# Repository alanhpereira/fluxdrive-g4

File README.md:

# fluxdrive-g4

Firmware, PC software and hardware design of a field-oriented-control (FOC) driver for 3-phase BLDC/PMSM motors, built as a graduation thesis (TCC) project.

- **Controller:** STSPIN32G4 (STM32G431 Cortex-M4F at 170 MHz with an integrated 3-phase gate driver), six 100 V MOSFETs, three 2 mΩ low-side shunts.
- **Control:** current loop at 25 kHz; speed and position loops at 2.5 kHz. Commutation from an MT6835 21-bit magnetic encoder, from the encoder with a back-EMF flux observer blended in at speed, or sensorless (high-frequency injection at standstill, the observer at speed).
- **Links:** USB-C (virtual COM port: telemetry, configuration, calibration) and CANopen (CiA 301 node, CiA 402 drive profile: PP, PV, HM, CSP, CSV, CST).
- **Protections:** overcurrent, over/undervoltage, regen clamp, overspeed, encoder loss, gate-driver faults. Stops coast instead of short-braking a spinning motor.
- **PC software:** a Python/Qt GUI with live plots, a parameter editor, a calibration wizard and a CANopen master, plus a CANopen test runner.

## Ratings and status

| | Designed for | Tested up to |
|---|---|---|
| Bus voltage | 70 V | 32 V |
| Phase current (continuous) | 15 A | 10 A |

This is a working prototype from a graduation thesis, not a finished product. Everything above the tested values is untested: the bridge MOSFETs are rated 100 V, but thermal performance, layout and protection behaviour at 70 V / 15 A have not been verified. The firmware defaults are conservative: overcurrent trip `imax` = 1.5 A and overvoltage trip `vbus_max` = 60 V; raise them deliberately for your motor and supply.

> [!WARNING]
> **This board switches high currents at voltages that can hurt you and destroy hardware.**
> - Bring up a new board, motor or firmware build from a **current-limited bench supply**, starting at low voltage and with a low `imax`.
> - A misconfigured or uncalibrated drive can **spin the motor suddenly and at full speed**. Clamp the motor and keep hands, cables and loose parts away from anything that rotates.
> - A spinning motor is a generator: it can push the bus voltage up (regeneration) or keep the phases live after the supply is off. Use a supply that tolerates reverse current, or a braking resistor/clamp, and wait for the motor to stop before touching it.
> - The MOSFETs, shunts and motor get hot. Watch the board temperature (Flux Studio shows it) and provide cooling above a few amps.
> - Use it at your own risk; see the licenses below (no warranty).

## Documentation

| Document | For |
|---|---|
| [docs/user-manual-driver.md](docs/user-manual-driver.md) | Using the driver: connections, flashing, commissioning a motor, run modes, protections, CANopen, parameter reference, troubleshooting |
| [docs/user-manual-software.md](docs/user-manual-software.md) | Using the PC software: Flux Studio (Scope, Config, CANopen tabs), test runner, helper scripts |
| [docs/developer-guide.md](docs/developer-guide.md) | Developer guide: build system, CubeMX rules, architecture, execution model, conventions |
| [docs/design-notes.md](docs/design-notes.md) | Design decisions, bench measurements and open items: config protocol, CANopen drive and PC tool, HFI, sensorless tuning, flash budget |
| [docs/software-structure.md](docs/software-structure.md) | Flowcharts of the software: modules, boot, main loop, PWM period, `currentLoop()`, protocol, telemetry, CANopen, trips, flash, PC tools, interrupt priorities |

## Repository layout

| Path | Content |
|---|---|
| `Core/` | Firmware: CubeMX-generated peripheral setup plus the hand-written control code (`motorCtrl.c`, `calib.c`, `hfi.c`, `mt6835.c`, `proto.c`, `objdict.c`, `params.c`, …) |
| `CANopen/` | CANopenNode stack, the FDCAN port, the object dictionary (exported from `fluxdrive-g4.xdd`) and the CiA 402 layer |
| `Drivers/`, `Middlewares/`, `USB_Device/` | ST HAL, CMSIS and USB device stack (generated) |
| `fluxdrive-g4.ioc` | STM32CubeMX project: the source of truth for the peripheral setup |
| `fluxdrive-g4.xdd` | CANopenEditor project of the object dictionary |
| `software/` | PC software: `fluxstudio.py` (GUI), `cotest.py` (CANopen tests), `fluxdrive-g4.eds` (EDS for CANopen masters) |
| `hardware/` | KiCad project of the board: schematic (controller, connections, power sheets) and PCB, the schematic as PDF (`fluxdrive-g4 schematic.pdf`). [hardware/README.md](hardware/README.md) links the datasheets of the main parts |
| `docs/` | Manuals and design notes |

## Quick start

### Firmware
Requirements: arm-none-eabi-gcc, make, OpenOCD and an ST-Link (paths in `.stm32env`). The project is set up for the **STM32 for VSCode** extension.

```
make -f STM32Make.make -j                                   # debug build -> build/debug/fluxdrive-g4.elf
make -f STM32Make.make -j flash                             # flash over ST-Link
make -f STM32Make.make -j DEBUG=0 OPTIMIZATION=-Os flash    # release build
```

A new board needs its option bytes set once before it boots from flash with CAN connected; see the driver manual, section 4.1. After the first flash, updates can also go over USB DFU (Config tab, **Reboot to DFU**, then STM32CubeProgrammer).

### PC software
```
pip install -r software/requirements.txt
python software/fluxstudio.py
```
Connect to the port marked **[driver USB]**, then follow the calibration steps in the Config tab (driver manual, section 5).

### Hardware
Open `hardware/fluxdrive-g4.kicad_pro` in KiCad (made with KiCad 10).

## License

- Firmware and PC software: MIT, see [LICENSE](LICENSE).
- Hardware (`hardware/`): CERN Open Hardware Licence Version 2 - Permissive (CERN-OHL-P-2.0), see [hardware/LICENSE](hardware/LICENSE).
- Third-party components keep their own licenses: CMSIS (Apache-2.0), the STM32G4 HAL (BSD-3-Clause), CANopenNode (Apache-2.0) and the ST USB device library (`Middlewares/ST/STM32_USB_Device_Library`, ST's SLA0044 license).

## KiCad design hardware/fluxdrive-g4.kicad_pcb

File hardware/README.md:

# Hardware

KiCad project of the fluxdrive-g4 board (made with KiCad 10): open `fluxdrive-g4.kicad_pro`. The root schematic holds three sheets (`01 - Controller`, `02 - Connections`, `03 - Power`); `fluxdrive-g4 schematic.pdf` is the same schematic as a PDF.

The hardware design files are licensed under the CERN Open Hardware Licence Version 2 - Permissive (CERN-OHL-P-2.0), see [LICENSE](LICENSE).

## Datasheets of the main parts

The datasheets are not in the repository (they are the manufacturers' documents). Download them from the links below; `hardware/datasheets/` is git-ignored, so local copies can go there.

| Part | Manufacturer | Role | Datasheet |
|---|---|---|---|
| STSPIN32G4 | STMicroelectronics | Controller: STM32G431 + 3-phase gate driver | [st.com](https://www.st.com/resource/en/datasheet/stspin32g4.pdf) |
| STM32G431VB | STMicroelectronics | The MCU inside the STSPIN32G4 | [st.com](https://www.st.com/resource/en/datasheet/stm32g431vb.pdf) |
| DI100N10PQ | Diotec | Bridge MOSFETs (100 V) | [diotec.com](https://diotec.com/request/datasheet/di100n10pq.pdf) |
| MT6835 | MagnTek (Novosense) | 21-bit magnetic encoder | [novosns.com](https://www.novosns.com/en/) (search for MT6835) |
| TJA1051 | NXP | CAN transceiver | [nxp.com](https://www.nxp.com/docs/en/data-sheet/TJA1051.pdf) |
| USBLC6-2 | STMicroelectronics | USB ESD protection | [st.com](https://www.st.com/resource/en/datasheet/usblc6-2.pdf) |
| ANTC1608-103F3450FB | APV Technologies | Board NTC (10 kΩ, B 3450 K, 0603) | [apvind.com](https://www.apvind.com/) (ANTC series) |

The STM32G4 reference manual (RM0440, register descriptions): [st.com](https://www.st.com/resource/en/reference_manual/rm0440-stm32g4-series-advanced-armbased-32bit-mcus-stmicroelectronics.pdf).

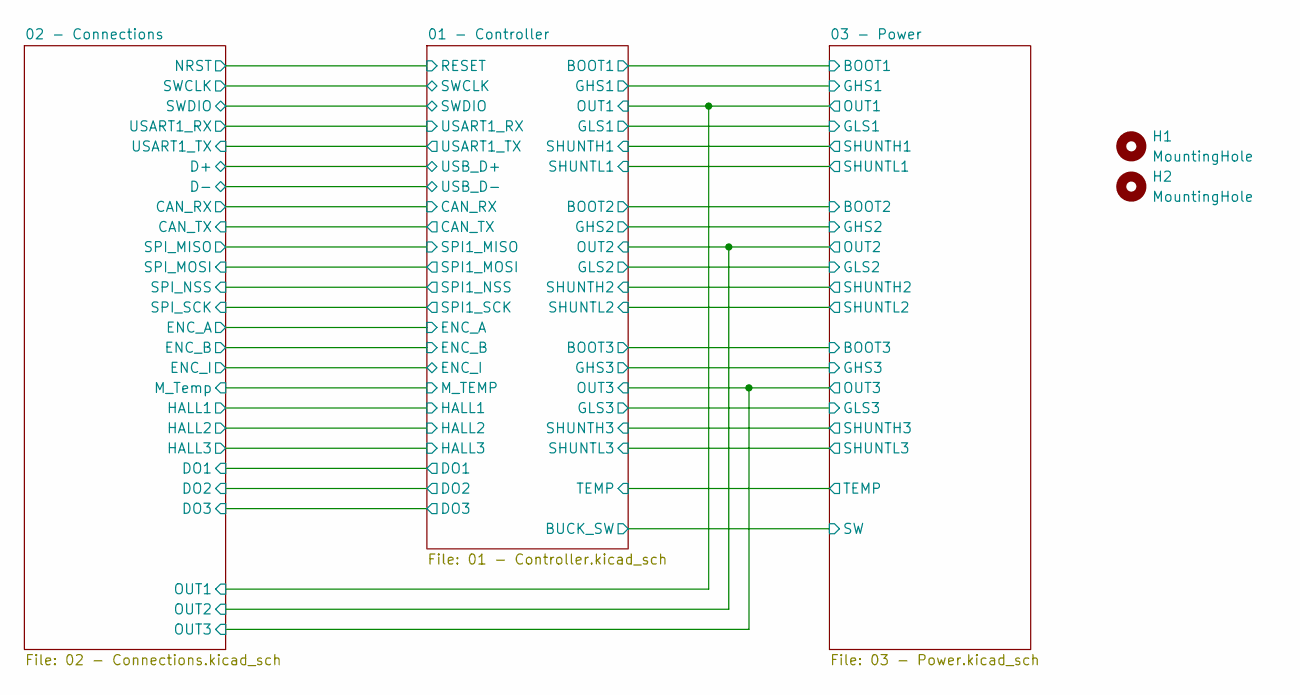
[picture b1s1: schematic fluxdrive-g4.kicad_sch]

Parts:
H1, H2: MountingHole; MountingHole_2.2mm_M2

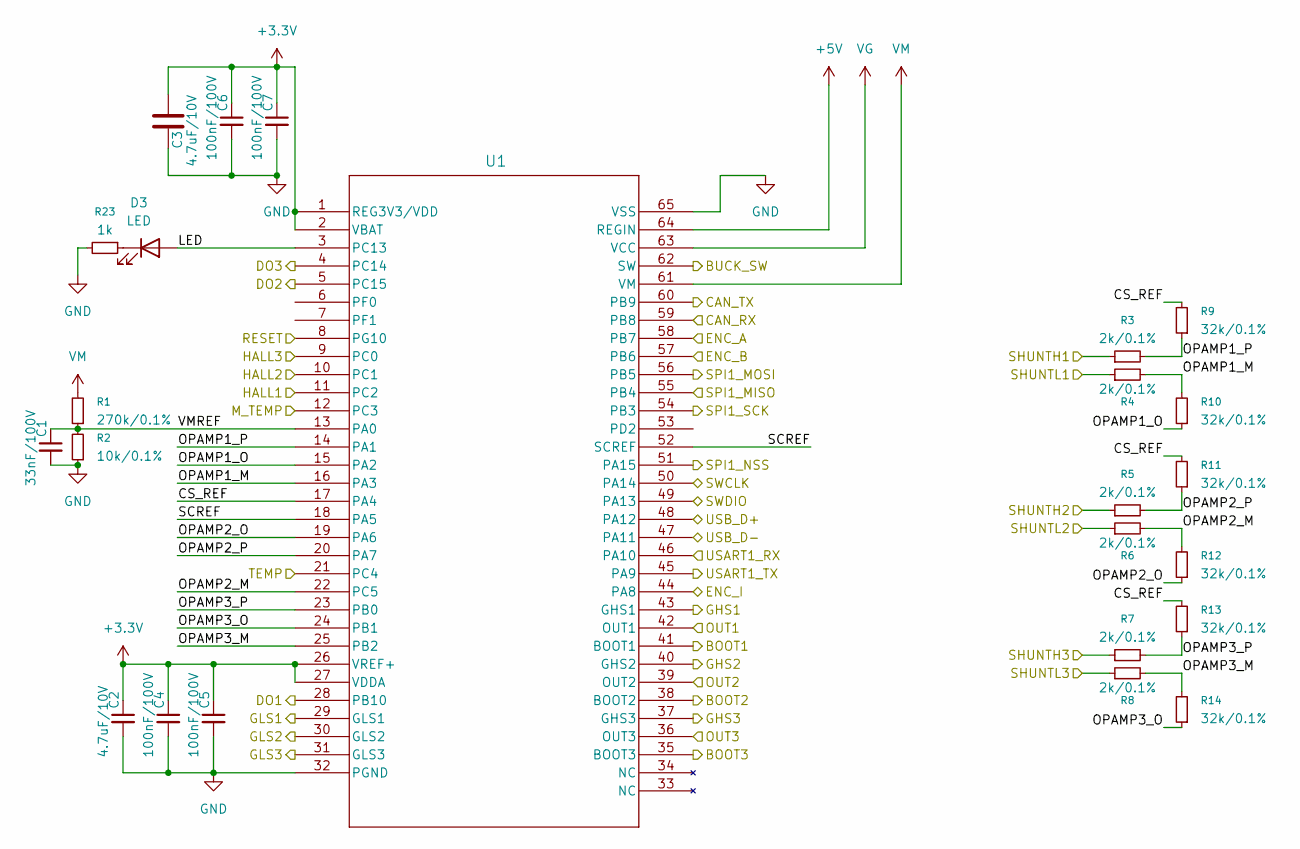
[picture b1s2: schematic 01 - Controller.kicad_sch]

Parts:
C1: 33nF/100V; C_0603_1608Metric
C2, C3: 4.7uF/10V; C_0603_1608Metric
C4, C5, C6, C7: 100nF/100V; C_0603_1608Metric
D3: LED; LED_0603_1608Metric
R1: 270k/0.1%; R_0603_1608Metric
R2: 10k/0.1%; R_0603_1608Metric
R3, R4, R5, R6, R7, R8: 2k/0.1%; R_0603_1608Metric
R9, R10, R11, R12, R13, R14: 32k/0.1%; R_0603_1608Metric
R23: 1k; R_0603_1608Metric
U1: STSPIN32G4TR; QFN_IN32G4_STM-L

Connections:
+3.3V: C2.1, C3.2, C4.1, C5.1, C6.1, C7.1, U1.1 (REG3V3/VDD), U1.2 (VBAT), U1.26 (VREF+), U1.27 (VDDA); also elsewhere on the board
+5V: U1.64 (REGIN); also elsewhere on the board
/01 - Controller/BOOT1: U1.41 (BOOT1); also elsewhere on the board
/01 - Controller/BOOT2: U1.38 (BOOT2); also elsewhere on the board
/01 - Controller/BOOT3: U1.35 (BOOT3); also elsewhere on the board
/01 - Controller/BUCK_SW: U1.62 (SW); also elsewhere on the board
/01 - Controller/CAN_RX: U1.59 (PB8); also elsewhere on the board
/01 - Controller/CAN_TX: U1.60 (PB9); also elsewhere on the board
/01 - Controller/CS_REF: R9.2, R11.2, R13.2, U1.17 (PA4)
/01 - Controller/DO1: U1.28 (PB10); also elsewhere on the board
/01 - Controller/DO2: U1.5 (PC15); also elsewhere on the board
/01 - Controller/DO3: U1.4 (PC14); also elsewhere on the board
/01 - Controller/ENC_A: U1.58 (PB7); also elsewhere on the board
/01 - Controller/ENC_B: U1.57 (PB6); also elsewhere on the board
/01 - Controller/ENC_I: U1.44 (PA8); also elsewhere on the board
/01 - Controller/GHS1: U1.43 (GHS1); also elsewhere on the board
/01 - Controller/GHS2: U1.40 (GHS2); also elsewhere on the board
/01 - Controller/GHS3: U1.37 (GHS3); also elsewhere on the board
/01 - Controller/GLS1: U1.29 (GLS1); also elsewhere on the board
/01 - Controller/GLS2: U1.30 (GLS2); also elsewhere on the board
/01 - Controller/GLS3: U1.31 (GLS3); also elsewhere on the board
/01 - Controller/HALL1: U1.11 (PC2); also elsewhere on the board
/01 - Controller/HALL2: U1.10 (PC1); also elsewhere on the board
/01 - Controller/HALL3: U1.9 (PC0); also elsewhere on the board
/01 - Controller/LED: D3.2 (A), U1.3 (PC13)
/01 - Controller/M_TEMP: U1.12 (PC3); also elsewhere on the board
/01 - Controller/OPAMP1_M: R4.2, R10.2, U1.16 (PA3)
/01 - Controller/OPAMP1_O: R10.1, U1.15 (PA2)
/01 - Controller/OPAMP1_P: R3.2, R9.1, U1.14 (PA1)
/01 - Controller/OPAMP2_M: R6.2, R12.2, U1.22 (PC5)
/01 - Controller/OPAMP2_O: R12.1, U1.19 (PA6)
/01 - Controller/OPAMP2_P: R5.2, R11.1, U1.20 (PA7)
/01 - Controller/OPAMP3_M: R8.2, R14.2, U1.25 (PB2)
/01 - Controller/OPAMP3_O: R14.1, U1.24 (PB1)
/01 - Controller/OPAMP3_P: R7.2, R13.1, U1.23 (PB0)
/01 - Controller/OUT1: U1.42 (OUT1); also elsewhere on the board
/01 - Controller/OUT2: U1.39 (OUT2); also elsewhere on the board
/01 - Controller/OUT3: U1.36 (OUT3); also elsewhere on the board
/01 - Controller/RESET: U1.8 (PG10); also elsewhere on the board
/01 - Controller/SCREF: U1.18 (PA5), U1.52 (SCREF)
/01 - Controller/SHUNTH1: R3.1; also elsewhere on the board
/01 - Controller/SHUNTH2: R5.1; also elsewhere on the board
/01 - Controller/SHUNTH3: R7.1; also elsewhere on the board
/01 - Controller/SHUNTL1: R4.1; also elsewhere on the board
/01 - Controller/SHUNTL2: R6.1; also elsewhere on the board
/01 - Controller/SHUNTL3: R8.1; also elsewhere on the board
/01 - Controller/SPI1_MISO: U1.55 (PB4); also elsewhere on the board
/01 - Controller/SPI1_MOSI: U1.56 (PB5); also elsewhere on the board
/01 - Controller/SPI1_NSS: U1.51 (PA15); also elsewhere on the board
/01 - Controller/SPI1_SCK: U1.54 (PB3); also elsewhere on the board
/01 - Controller/SWCLK: U1.50 (PA14); also elsewhere on the board
/01 - Controller/SWDIO: U1.49 (PA13); also elsewhere on the board
/01 - Controller/TEMP: U1.21 (PC4); also elsewhere on the board
/01 - Controller/USART1_RX: U1.46 (PA10); also elsewhere on the board
/01 - Controller/USART1_TX: U1.45 (PA9); also elsewhere on the board
/01 - Controller/USB_D+: U1.48 (PA12); also elsewhere on the board
/01 - Controller/USB_D-: U1.47 (PA11); also elsewhere on the board
/01 - Controller/VMREF: C1.1, R1.1, R2.2, U1.13 (PA0)
GND: C1.2, C2.2, C3.1, C4.2, C5.2, C6.2, C7.2, R2.1, R23.2, U1.32 (PGND), U1.65 (VSS); also elsewhere on the board
unnamed: D3.1 (K), R23.1
VG: U1.63 (VCC); also elsewhere on the board
VM: R1.2, U1.61 (VM); also elsewhere on the board

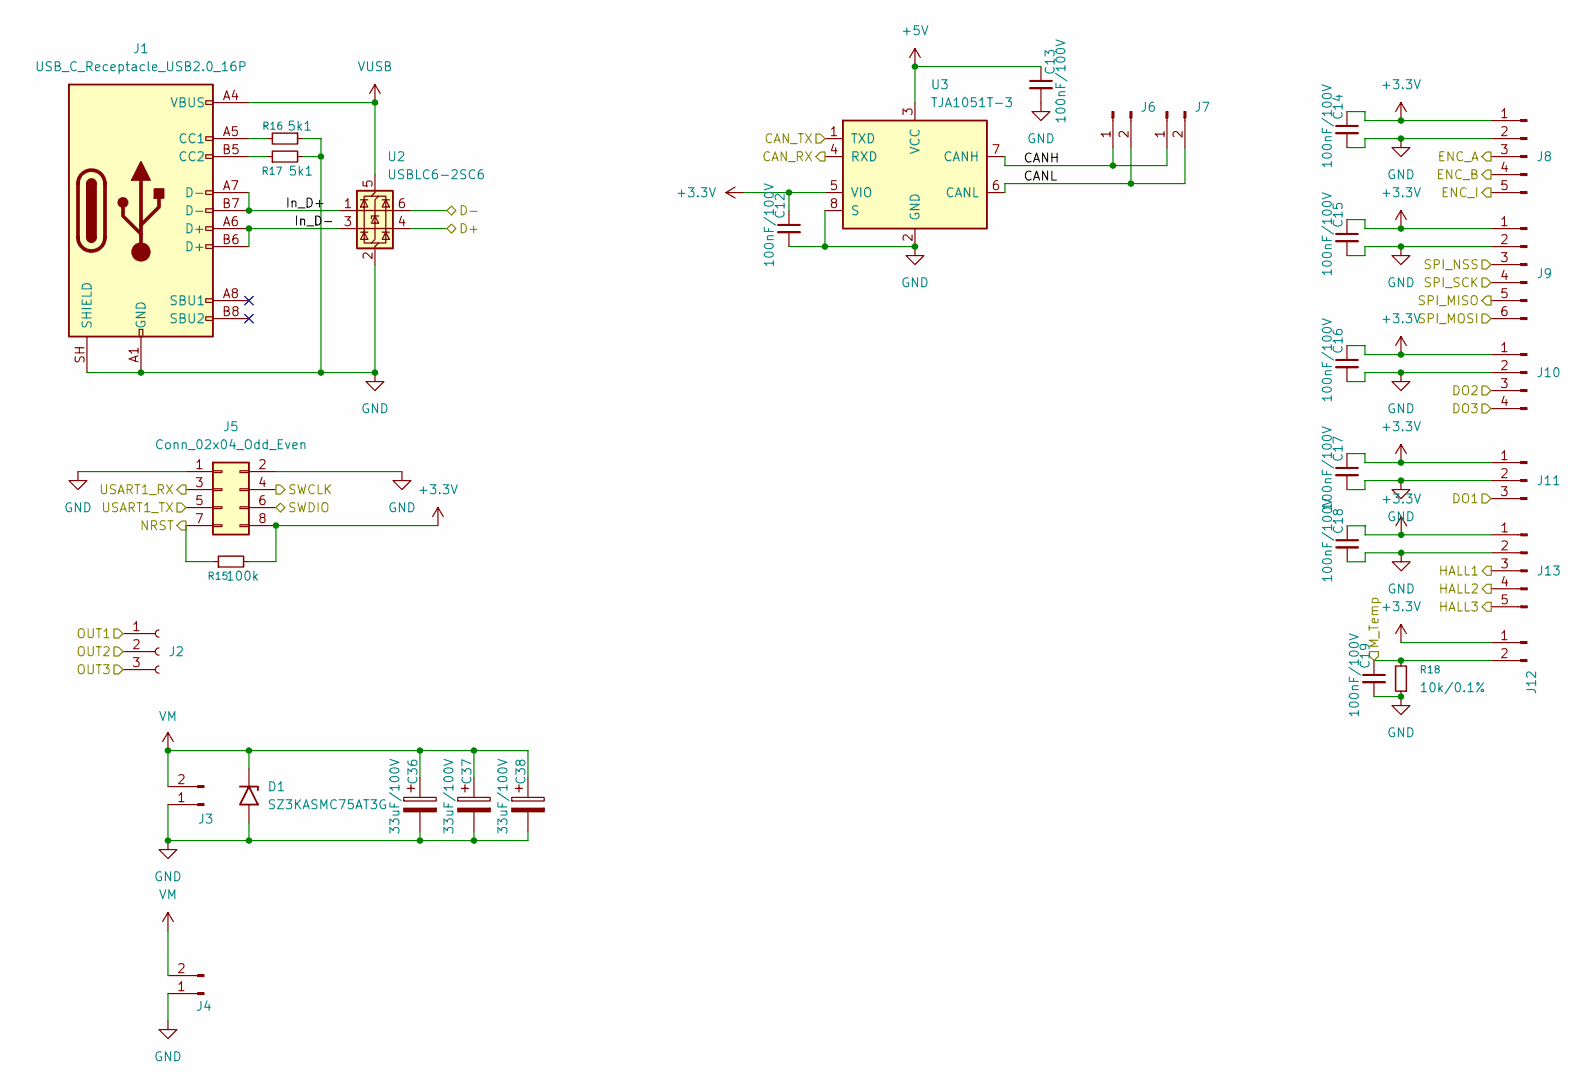
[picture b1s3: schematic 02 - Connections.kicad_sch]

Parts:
C12, C13, C14, C15, C16, C17, C18, C19: 100nF/100V; C_0603_1608Metric
C36, C37, C38: 33uF/100V; CP_Radial_D8.0mm_P3.50mm
D1: SZ3KASMC75AT3G; D_SMC
J1: USB_C_Receptacle_USB2.0_16P; USB_C_Receptacle_HRO_TYPE-C-31-M-12; LCSC Part C165948
J2: Conn_01x03_Socket; CONN-TH_3P-P3.50_MR30PB-F30.G.Y
J3, J4: Conn_01x02_Pin; AMASS_XT30UPB-M
J5: Conn_02x04_Odd_Even; PinHeader_2x04_P2.54mm_Vertical
J6, J7, J12: Conn_01x02_Pin; JST_PH_B2B-PH-K_1x02_P2.00mm_Vertical
J8, J13: Conn_01x05_Pin; JST_PH_B5B-PH-K_1x05_P2.00mm_Vertical
J9: Conn_01x06_Pin; JST_PH_B6B-PH-K_1x06_P2.00mm_Vertical
J10: Conn_01x04_Pin; JST_PH_B4B-PH-K_1x04_P2.00mm_Vertical
J11: Conn_01x03_Pin; JST_PH_B3B-PH-K_1x03_P2.00mm_Vertical
R15: 100k; R_0603_1608Metric
R16, R17: 5k1; R_0603_1608Metric
R18: 10k/0.1%; R_0603_1608Metric
U2: USBLC6-2SC6; SOT-23-6; LCSC Part C2827654
U3: TJA1051T-3; SOIC-8_3.9x4.9mm_P1.27mm

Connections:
+3.3V: C12.1, C14.1, C15.1, C16.1, C17.1, C18.1, J5.8, J8.1, J9.1, J10.1, J11.1, J12.1, J13.1, R15.2, U3.5 (VIO); also elsewhere on the board
+5V: C13.1, U3.3 (VCC); also elsewhere on the board
/01 - Controller/CAN_RX: U3.4 (RXD); also elsewhere on the board
/01 - Controller/CAN_TX: U3.1 (TXD); also elsewhere on the board
/01 - Controller/DO1: J11.3; also elsewhere on the board
/01 - Controller/DO2: J10.3; also elsewhere on the board
/01 - Controller/DO3: J10.4; also elsewhere on the board
/01 - Controller/ENC_A: J8.3; also elsewhere on the board
/01 - Controller/ENC_B: J8.4; also elsewhere on the board
/01 - Controller/ENC_I: J8.5; also elsewhere on the board
/01 - Controller/HALL1: J13.3; also elsewhere on the board
/01 - Controller/HALL2: J13.4; also elsewhere on the board
/01 - Controller/HALL3: J13.5; also elsewhere on the board
/01 - Controller/M_TEMP: C19.1, J12.2, R18.2; also elsewhere on the board
/01 - Controller/OUT1: J2.1; also elsewhere on the board
/01 - Controller/OUT2: J2.2; also elsewhere on the board
/01 - Controller/OUT3: J2.3; also elsewhere on the board
/01 - Controller/RESET: J5.7, R15.1; also elsewhere on the board
/01 - Controller/SPI1_MISO: J9.5; also elsewhere on the board
/01 - Controller/SPI1_MOSI: J9.6; also elsewhere on the board
/01 - Controller/SPI1_NSS: J9.3; also elsewhere on the board
/01 - Controller/SPI1_SCK: J9.4; also elsewhere on the board
/01 - Controller/SWCLK: J5.4; also elsewhere on the board
/01 - Controller/SWDIO: J5.6; also elsewhere on the board
/01 - Controller/USART1_RX: J5.3; also elsewhere on the board
/01 - Controller/USART1_TX: J5.5; also elsewhere on the board
/01 - Controller/USB_D+: U2.4 (I/O2); also elsewhere on the board
/01 - Controller/USB_D-: U2.6 (I/O1); also elsewhere on the board
/02 - Connections/CANH: J6.1, J7.1, U3.7 (CANH)
/02 - Connections/CANL: J6.2, J7.2, U3.6 (CANL)
/02 - Connections/In_D+: J1.A7 (D-), J1.B7 (D-), U2.1 (I/O1)
/02 - Connections/In_D-: J1.A6 (D+), J1.B6 (D+), U2.3 (I/O2)
GND: C12.2, C13.2, C14.2, C15.2, C16.2, C17.2, C18.2, C19.2, C36.2, C37.2, C38.2, D1.2 (A2), J1.A1 (GND), J1.A12 (GND), J1.B1 (GND), J1.B12 (GND), J1.SH (SHIELD), J3.1, J4.1, J5.1, J5.2, J8.2, J9.2, J10.2, J11.2, J13.2, R16.1, R17.2, R18.1, U2.2 (GND), U3.2 (GND), U3.8 (S); also elsewhere on the board
unnamed: J1.A5 (CC1), R16.2
unnamed: J1.B5 (CC2), R17.1
VM: C36.1, C37.1, C38.1, D1.1 (A1), J3.2, J4.2; also elsewhere on the board
VUSB: J1.A4 (VBUS), J1.A9 (VBUS), J1.B4 (VBUS), J1.B9 (VBUS), U2.5 (VBUS); also elsewhere on the board

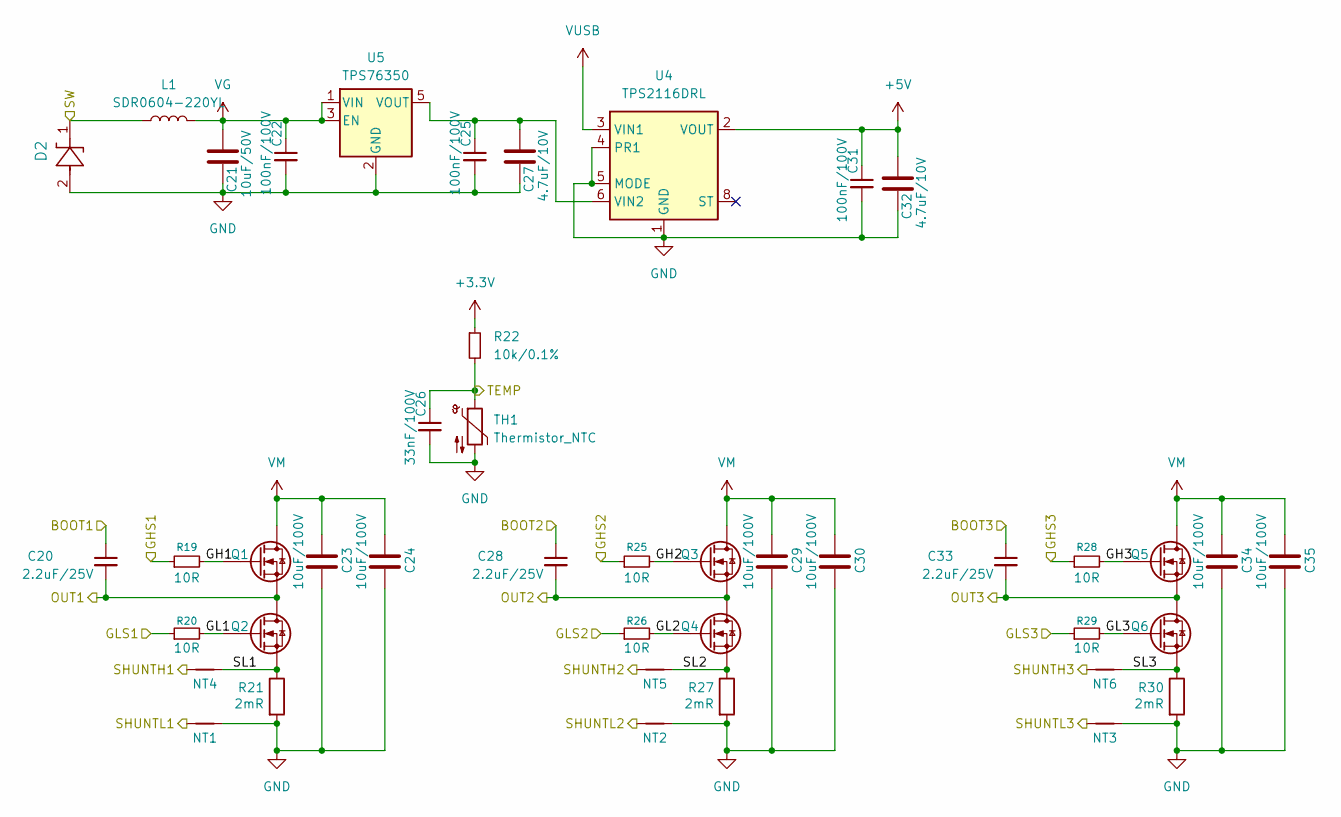
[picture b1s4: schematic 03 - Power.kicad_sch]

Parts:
C20, C28, C33: 2.2uF/25V; C_0603_1608Metric
C21: 10uF/50V; C_1206_3216Metric
C22, C25, C31: 100nF/100V; C_0603_1608Metric
C23, C24, C29, C30, C34, C35: 10uF/100V; C_1210_3225Metric
C26: 33nF/100V; C_0603_1608Metric
C27, C32: 4.7uF/10V; C_0603_1608Metric
D2: STPS1H100A; SMA_STM-L
L1: SDR0604-220YL; L_Bourns_SDR0604
NT1, NT2, NT3, NT4, NT5, NT6: NetTie_2; NetTie-2_SMD_Pad0.1mm
Q1, Q2, Q3, Q4, Q5, Q6: DI100N10PQ; P260_QFN5x6_TDSON-8
R19, R20, R25, R26, R28, R29: 10R; R_0603_1608Metric
R21, R27, R30: 2mR; R_0612_1632Metric
R22: 10k/0.1%; R_0603_1608Metric
TH1: Thermistor_NTC; R_0603_1608Metric
U4: TPS2116DRL; SOT-583-8
U5: TPS76350; SOT-23-5

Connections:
+3.3V: R22.1; also elsewhere on the board
+5V: C31.1, C32.2, U4.2 (VOUT), U4.7 (VOUT); also elsewhere on the board
/01 - Controller/BOOT1: C20.1; also elsewhere on the board
/01 - Controller/BOOT2: C28.1; also elsewhere on the board
/01 - Controller/BOOT3: C33.1; also elsewhere on the board
/01 - Controller/BUCK_SW: D2.1, L1.1; also elsewhere on the board
/01 - Controller/GHS1: R19.1; also elsewhere on the board
/01 - Controller/GHS2: R25.1; also elsewhere on the board
/01 - Controller/GHS3: R28.1; also elsewhere on the board
/01 - Controller/GLS1: R20.1; also elsewhere on the board
/01 - Controller/GLS2: R26.1; also elsewhere on the board
/01 - Controller/GLS3: R29.1; also elsewhere on the board
/01 - Controller/OUT1: C20.2, Q1.S, Q2.D; also elsewhere on the board
/01 - Controller/OUT2: C28.2, Q3.S, Q4.D; also elsewhere on the board
/01 - Controller/OUT3: C33.2, Q5.S, Q6.D; also elsewhere on the board
/01 - Controller/SHUNTH1: NT4.1; also elsewhere on the board
/01 - Controller/SHUNTH2: NT5.1; also elsewhere on the board
/01 - Controller/SHUNTH3: NT6.1; also elsewhere on the board
/01 - Controller/SHUNTL1: NT1.1; also elsewhere on the board
/01 - Controller/SHUNTL2: NT2.1; also elsewhere on the board
/01 - Controller/SHUNTL3: NT3.1; also elsewhere on the board
/01 - Controller/TEMP: C26.1, R22.2, TH1.1; also elsewhere on the board
/03 - Power/GH1: Q1.G, R19.2
/03 - Power/GH2: Q3.G, R25.2
/03 - Power/GH3: Q5.G, R28.2
/03 - Power/GL1: Q2.G, R20.2
/03 - Power/GL2: Q4.G, R26.2
/03 - Power/GL3: Q6.G, R29.2
/03 - Power/SL1: NT4.2, Q2.S, R21.1
/03 - Power/SL2: NT5.2, Q4.S, R27.1
/03 - Power/SL3: NT6.2, Q6.S, R30.1
GND: C21.1, C22.2, C23.2, C24.2, C25.2, C26.2, C27.1, C29.2, C30.2, C31.2, C32.1, C34.2, C35.2, D2.2, NT1.2, NT2.2, NT3.2, R21.2, R27.2, R30.2, TH1.2, U4.1 (GND), U4.4 (PR1), U4.5 (MODE), U5.2 (GND); also elsewhere on the board
unnamed: C25.1, C27.2, U4.6 (VIN2), U5.5 (VOUT)
VG: C21.2, C22.1, L1.2, U5.1 (VIN), U5.3 (EN); also elsewhere on the board
VM: C23.1, C24.1, C29.1, C30.1, C34.1, C35.1, Q1.D, Q3.D, Q5.D; also elsewhere on the board
VUSB: U4.3 (VIN1); also elsewhere on the board

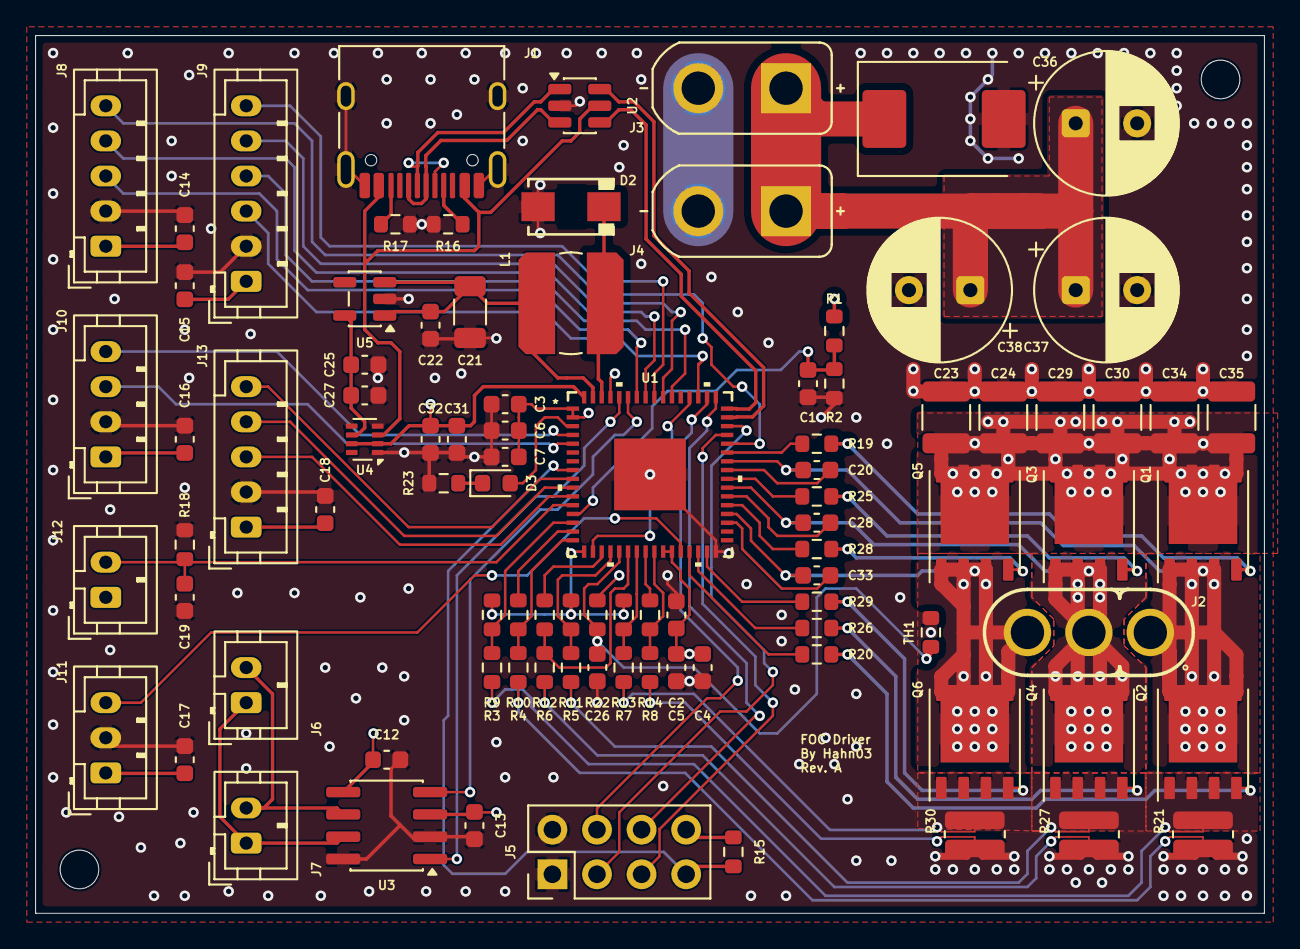
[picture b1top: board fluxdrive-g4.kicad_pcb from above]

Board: 4 copper layers, 70.0 x 50.0 mm, 100 parts (0 on the bottom side), 79 nets.

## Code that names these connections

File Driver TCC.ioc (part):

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Mcu.Name=STM32G431V(6-8-B)Tx
Mcu.Package=LQFP100
Mcu.UserName=STM32G431VBTx
PA0.GPIOParameters=GPIO_Label
PA0.GPIO_Label=VIN_REF
PA0.Mode=IN1-Single-Ended
PA0.Signal=ADC2_IN1
PA1.Mode=Standalone
PA1.Signal=OPAMP1_VINP
PA10.Mode=Asynchronous
PA10.Signal=USART1_RX
PA11.Mode=Device
PA11.Signal=USB_DM
PA12.Mode=Device
PA12.Signal=USB_DP
PA13.Mode=Serial_Wire
PA13.Signal=SYS_JTMS-SWDIO
PA14.Mode=Serial_Wire
PA14.Signal=SYS_JTCK-SWCLK
PA15.GPIOParameters=GPIO_Label
PA15.GPIO_Label=SPI_NCS
PA15.Signal=GPIO_Output
PA2.GPIOParameters=GPIO_Label
PA2.GPIO_Label=CS1
PA2.Signal=SharedAnalog_PA2
PA3.Mode=Standalone
PA3.Signal=OPAMP1_VINM
PA4.GPIOParameters=GPIO_Label
PA4.GPIO_Label=CS_REF
PA4.Signal=COMP_DAC11_group
PA5.GPIOParameters=GPIO_Label
PA5.GPIO_Label=SCREF
PA5.Signal=COMP_DAC12_group
PA6.GPIOParameters=GPIO_Label
PA6.GPIO_Label=CS2
PA6.Signal=SharedAnalog_PA6
PA7.Mode=Standalone
PA7.Signal=OPAMP2_VINP
PA8.GPIOParameters=GPIO_Label
PA8.GPIO_Label=ENC_I
PA8.Signal=S_TIM4_ETR
PA9.Mode=Asynchronous
PA9.Signal=USART1_TX
PB0.Mode=Standalone
PB0.Signal=OPAMP3_VINP
PB1.GPIOParameters=GPIO_Label
PB1.GPIO_Label=CS3
PB1.Signal=SharedAnalog_PB1
PB10.Signal=GPIO_Output
PB2.Mode=Standalone
PB2.Signal=OPAMP3_VINM
PB3.Mode=Full_Duplex_Master
PB3.Signal=SPI1_SCK
PB4.Mode=Full_Duplex_Master
PB4.Signal=SPI1_MISO
PB5.Mode=Full_Duplex_Master
PB5.Signal=SPI1_MOSI
PB6.Signal=S_TIM4_CH1
PB7.Signal=S_TIM4_CH2
PB8-BOOT0.Mode=FDCAN_Activate
PB8-BOOT0.Signal=FDCAN1_RX
PB9.Mode=FDCAN_Activate
PB9.Signal=FDCAN1_TX
PC0.GPIOParameters=GPIO_Label
PC0.GPIO_Label=HALL3
PC0.Signal=GPXTI0
PC1.GPIOParameters=GPIO_Label
PC1.GPIO_Label=HALL2
PC1.Signal=GPXTI1
PC13.Signal=GPIO_Output
PC14-OSC32_IN.Signal=GPIO_Input
PC15-OSC32_OUT.Signal=GPIO_Output
PC2.GPIOParameters=GPIO_Label
PC2.GPIO_Label=HALL1
PC2.Signal=GPXTI2
PC3.GPIOParameters=GPIO_Label
PC3.GPIO_Label=MOT_TEMP
PC3.Mode=IN9-Single-Ended
PC3.Signal=ADC1_IN9
PC4.GPIOParameters=GPIO_Label
PC4.GPIO_Label=DRV_TEMP
PC4.Mode=IN5-Single-Ended
PC4.Signal=ADC2_IN5
PC5.Mode=Standalone
PC5.Signal=OPAMP2_VINM
PC8.Mode=I2C
PC8.Signal=I2C3_SCL
PC9.Mode=I2C
PC9.Signal=I2C3_SDA
PE10.GPIOParameters=GPIO_Label
PE10.GPIO_Label=GLS2
PE10.Mode=PWM Generation2 CH2 CH2N
PE10.Signal=TIM1_CH2N
PE11.GPIOParameters=GPIO_Label
PE11.GPIO_Label=GHS2
PE11.Signal=S_TIM1_CH2
PE12.GPIOParameters=GPIO_Label
PE12.GPIO_Label=GLS3
PE12.Mode=PWM Generation3 CH3 CH3N
PE12.Signal=TIM1_CH3N
PE13.GPIOParameters=GPIO_Label
PE13.GPIO_Label=GHS3
PE13.Signal=S_TIM1_CH3
PE14.GPIOParameters=GPIO_PuPd,GPIO_Label
PE14.GPIO_Label=DRV_RDY
PE14.GPIO_PuPd=GPIO_PULLUP
PE14.Signal=GPIO_Input
PE15.Mode=Activate-Break-Input
PE15.Signal=TIM1_BKIN
PE7.GPIOParameters=GPIO_Label
PE7.GPIO_Label=Wake
PE7.Signal=GPIO_Output
PE8.GPIOParameters=GPIO_Label
PE8.GPIO_Label=GLS1
PE8.Mode=PWM Generation1 CH1 CH1N
PE8.Signal=TIM1_CH1N
PE9.GPIOParameters=GPIO_Label
PE9.GPIO_Label=GHS1
PE9.Signal=S_TIM1_CH1
RCC.HSE_VALUE=8000000
RCC.SYSCLKFreq_VALUE=170000000
RCC.SYSCLKSource=RCC_SYSCLKSOURCE_PLLCLK
board=custom
